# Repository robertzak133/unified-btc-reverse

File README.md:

# unified-btc-reverse

This repository contains tools, source file, hand patches, and documentation for the (nearly) complete flow for adding new features, written in C, to Browning Trail Cameras via semi-automatically generated firmware update files.  Supported cameras are BTC-7A, BTC{7,8}{E, E-HP4, E-HP5}.  That is, Browning Recon Force Advantage, and Recon Force  and Spec Ops line of cameras, models Edge, Elite HP4, and Elite HP5.

Note that installing this firmware may void the manufacturer warranty.  If you need to return a camera to the manufacture for warranty, see instructions below for "Reinstalling Factory Firmware" to first get the camera back into original factory configuration.  

## Most Recent Releases
2025-03-02: 

A major release, including new functions, and generalization of  previous functions. 

I have also updated the firmare for the HP5 cameras so that they are based on the more recent factory firmware, version "M06170F." I'm not sure what's new in this factory release, although I don't believe it addresses the "corrupt SD card" bug.  My fix for this bug remains in place.

I added support for the BTC-7A (Recon Force Advantage) model.  This firmware is based on the more recent model for the BTC-7E, and thus inherits the "capture timer" feature Bronwning introduced with the "Elite" models.

I added Several new features, described in more detail below.  These include: 

* Saving and Restoring Custom Settings

* Native Photo Quality

* External Trigger

I have also removed the "Extended SD Card" menu.  This was a lightly used, and likely obsolete function, and I needed to retire it to make room for the custom configuration code, above.

As of 2025-03-18, there is a known issue that prevents certain newer HP5 cameras from downloading this firmware (or Browning firmware, for that matter).  If the "YES" option isn't available in the "FW UPGRADE" menu, you may have one of these cameras. 

See notes below for a description of how these new features might be used.  

## Feature Description
See also articles describing features at [New Optional Features for Browning HP5 Trail Cameras](https://winterberrywildlife.ouroneacrefarm.com/2022/12/19/new-optional-features-for-browning-hp5-trail-cameras/)
and 
[Adding Features to Browning Elite HP5 Firmware](https://winterberrywildlife.ouroneacrefarm.com/2022/11/14/adding-features-to-browning-elite-hp5-firmware/)

## Released Firmware Images
If you are here for RELEASE'd firmware images themselves, you can find them below:
| Camera Model | Factory Baseline  | Current WBWL | Version  | Build Date |
|--------------|-------------------|--------------|----------|------------|
| BTC-7A | [brnbtc70.BRN](https://github.com/robertzak133/unified-btc-reverse/blob/main/targets/btc-7a/factory-firmware-images/BTC7E_2021_10_07/brnbtc70.BRN) | [brnbtc70.BRN](https://github.com/robertzak133/unified-btc-reverse/blob/main/targets/btc-7a/created-burn-images/RELEASE/brnbtc70.BRN) | WWL7A_250321R | 2025-03-21 |
| BTC-7E | [brnbtc70.BRN](https://github.com/robertzak133/unified-btc-reverse/blob/main/targets/btc-7e/factory-firmware-images/BTC7E_2021_10_07/brnbtc70.BRN) | [brnbtc70.BRN](https://github.com/robertzak133/unified-btc-reverse/blob/main/targets/btc-7e/created-burn-images/RELEASE/brnbtc70.BRN) | WWL7E_250321R | 2025-03-21 |
| BTC-8E | [brnbtc80.BRN](https://github.com/robertzak133/unified-btc-reverse/blob/main/targets/btc-8e/factory-firmware-images/BTC8E_2021_10_07/brnbtc80.BRN) | [brnbtc80.BRN](https://github.com/robertzak133/unified-btc-reverse/blob/main/targets/btc-8e/created-burn-images/RELEASE/brnbtc80.BRN) | WWL8E_250321R | 2025-03-21 |
| BTC-7E-HP4 | [brnbtc71.BRN](https://github.com/robertzak133/unified-btc-reverse/blob/main/targets/btc-7e-hp4/factory-firmware-images/2023-02-01-ns/brnbtc71.BRN) | [brnbtc71.BRN](https://github.com/robertzak133/unified-btc-reverse/blob/main/targets/btc-7e-hp4/created-burn-images/RELEASE/brnbtc71.BRN) | WWL7EH4_250321R | 2025-03-21 |
| BTC-8E-HP4 | [brnbtc81.BRN](https://github.com/robertzak133/unified-btc-reverse/blob/main/targets/btc-8e-hp4/factory-firmware-images/2023-02-01-ns/brnbtc81.BRN) | [brnbtc81.BRN](https://github.com/robertzak133/unified-btc-reverse/blob/main/targets/btc-8e-hp4/created-burn-images/RELEASE/brnbtc81.BRN) | WWL8EH4_250321R | 2025-03-21 |
| BTC-7E-HP5 | [brnbtc72.BRN](https://github.com/robertzak133/unified-btc-reverse/blob/main/targets/btc-7e-hp5/factory-firmware-images/BTC7EH5_M06170F/brnbtc72.BRN) | [brnbtc72.BRN](https://github.com/robertzak133/unified-btc-reverse/blob/main/targets/btc-7e-hp5/created-burn-images/RELEASE/brnbtc72.BRN) | WWL7EH5_250321R | 2025-03-21 |
| BTC-8E-HP5 | [brnbtc82.BRN](https://github.com/robertzak133/unified-btc-reverse/blob/main/targets/btc-8e-hp5/factory-firmware-images/BTC8EH5_M06170F/brnbtc82.BRN) | [brnbtc82.BRN](https://github.com/robertzak133/unified-btc-reverse/blob/main/targets/btc-8e-hp5/created-burn-images/RELEASE/brnbtc82.BRN) | WWL8EH5_250321R | 2025-03-21 |

## Download Instructions
- Find the copy of brnbtc7x.BRN (Recon Force) or brnbtc8x.BRN (Spec Ops) file for your camera above
- Click "Download Raw".  Resulting file should be approximateley 4-6 MBytes in length.  
- Copy this file onto an SD card at the "top level" (not into a folder on SD card).  
- Note -- the file must be named "brnbtc7x.BRN" (for Recon Force) or "brnbtc8x.BRN" (for Spec Ops), where "x" is model dependent.  Sometimes downloading from your browser will add extra characters to distinguish it from previous downloads -- e.g. "brnbtc72(1).BRN".  If this happens, rename file to eliminate the extra character. In this case, to  "brnbtc72.BRN". 

## FW install Instructions

Before installing new firmware, make sure you have batteries that will easily power the camera for the several minutes it takes for firmware upgrade. Losing power during firmware upgrade is bad, requiring that the camera be reprogrammed by the manufacturer.  

On the Camera:
- Press "Mode" button 
- Select "CAMERA SETUP"
- Select "FW UPGRADE"
- Select "YES"

Display should show "UPGRADING".  Loading the firmware should take about 20 seoconds. DO NOT TURN OFF OR REMOVE BATTERIES DURING THIS TIME! (this will "brick" the camera).  

Camera will then "Reboot" with new firmware.

Note that updating firmware resets the camera configuration settings, including the date and time. 

## Reinstalling Factory Firmware
If, for any reason, you want to get back to the factory firmware, choose the "Factory Baseline" entry in the table above to get the baseline factory image, and install that.

Note that in order to restore the factory firmware to a BTC-7A camera, it is necessary to install the factory firmware twice, in succession, in order to work around incompatiblities between the firmware loader original to the BTC-7A, and that of the BTC-7E (which I used as the baseline for the custom BTC-7A firmware).  

## Feature Summary
 * Custom Ribbon: In "Playback" menu, the date and time of the photo/video are shown is larger font at the bottom of the playback screen, making it easier to tell when the image was taken when reviewing in the field. 
 * Night Video Limit: The default manufacturer firmware limits night time (flash illuminated) videos to 20 Seconds.  This option removes that limit, allowing illuminated videos of the same duration as daylight videos.
 * Custom Info Strip: Adds "seconds" to the time of day; adds battery percent; compresses the size of the Browning logo so it doesn't extend up into the main screen space. 
 * Custom Volume/Directory/Filenames: Normally, this camera renames the SD card "volume"  to "BROWNING", in folders in DCIM called xxxBTCF, in files called IMG_xxxx.  With this modification, these labels are all taken from the camera name, as set by the user.  Note that only the first 5 and 4 characters are used for the folder and file suffix/prefix respectively.  Thus, for camera name, "MYCAMERA", the SD card will be labeled "MYCAMERA" and files can be found in DCIM/100MYCAME/MYCA0001.JPG.  Any "space" in the first 5 characters is replaced by an "underscore".
 * External Trigger: In the "DSLR" and "FLASH" settings, causes the "aim led" to turned on to trigger an external camera or external flashes.  In the "DSLR" setting, the aim test LED is set whenever a photo or video is taken.  In the "FLASH" setting the "aim led" is only turned on during low light conditions.  This can be used to trigger external flashes, which are only used at night.
 * Time and Date Format Options: Added options for time format -- 12H/24H; and date formats MM/DD/YYYY; DD/MM/YYYY; YYYY/MM/DD; and YYYYMMDD
 * IR Flash Power: Added an "Off" option to IR Flash power.  When "Off", the internal IR Flash is not used, even for night photos.  Intended for use in sets with another source of IR or White Flash illumination. 
 * Night Threshold: Lowers the amount of light required to take a color image.  Defaults to "Standard".  In the "Always Color" setting, the camera will take color photos even in darkness.  Useful with external illumination, or when converting a camera to white flash.  
 * Timelapse+ Mode Enhancements:
 
   * More Frequent Timelapse Options: I added (every) "1" and "2" second options to the Timelapse Frequency Menu.  

   * All Day/Night Timelapse Period:  The factory firmware does it's best to limit timelapse photos to daytime only.  The factory "timelapse period" menu allows you to restrict daytime photos to 1,2,3, or 4 hours after sunrise and before sunset; or to take photos "all day".  For some applications, it is desirable to take 24 hour timelapse footage.  Thus, I have added an "all day/night" menu entry.  In this mode the camera will take a photo 24/7 at the specified interval.  In the "ALL DAY/NIGHT" mode, a new .TLS file is created every at midnight, per the local clock. This creates a separate .TLS file every 24 hours.   
   * When operating in "All Day/Night" timelapse period, the CAPTURE_TIMER can be used to exclude periods of the day from timelapse photos.  
   * PIR Triggers always stored as JPG: In the factory firmware, PIR triggered photos are stored with the Timelpase photos in the .TLS file if they occur during the day.  If at night, they are stored as individual JPG images.  With my new firmware, all PIR triggered photos are stored as JPG images, making it easier to separate timelapse vs. PIR triggered images. 
   * Timelapse Format: A new menu selects whether to store images taken in Timelapse+ mode as .TLS files (factory default), or as a series of .JPG files (new feature).  This feature designed to support data processing of Timelapse images as single JPGs (e.g. an AI-based tool flow which starts with JPG images).  

* Fix to SD Corruption Issue: fixes a bug in factory firmware in which SD cards are sometimes corrupted.  This fix allows higher speed (and higer capacity) SD cards to work reliably in Edge, HP4, and HP5 models. 

 * Loading/Storing Custom Configuration to SD card: This feature allows users to save a custom configuration to a file on the SD card.  Selecting the "SAVE CUSTOM" option in the "DEFAULT SETTINGs" menu will save a copy of the current camera settings to a file on the SD card.  If an SD card contains a valid configuruation file, the "CUSTOM" entry will be selectable, and will load the configuration in the file into the camera.   SD cards can be used in multiple cameras to bring them all to a user-specific configuration quickly, and without errors associated with updating the configuration by hand. Note that configurations are camera model-specific, and separate configuration files are required for each different camera model.  The (load)"FACTORY" option returns the camera to the factory configuration.  
 * Native Photo Quality: I added a "Native" selection to the "Photo Quality" menu.  This will cause photos to be taken at the native resolution of the Sony sensor, which is 1920 * 1080 pixels [2 MPixels].  This is the same resolution used by the factory firmware to take timelapse photos, and to take "rapid burst" photos.  This feature may be useful when collecting photos for an AI-based backend processing pipeline.  

## Features no longer supported

 * Extended SD Power: Causes the CPU and SD card to remain powered on for 30 seconds after each photo or video.  This to allow shared SD card to be read by another device.  Note that during this time, the camera will not trigger.

## Build environment and Source Code

This repository contains tools and source code for building firmware images.  

This is the third reorganziation of this effort, and it is aimed at preserving as much commonality between camera platforms as possible.  For example, by containing a single set of tools and source code for all targeted cameras.

Start at [Google Colab worksheet](https://github.com/robertzak133/unified-btc-reverse/blob/main/tools/colab/2023-01-30-Unified-BTC-BRN-FIle-Creator.ipynb) 

More detailed documentation to come in future blog posts, which will be referenced here.

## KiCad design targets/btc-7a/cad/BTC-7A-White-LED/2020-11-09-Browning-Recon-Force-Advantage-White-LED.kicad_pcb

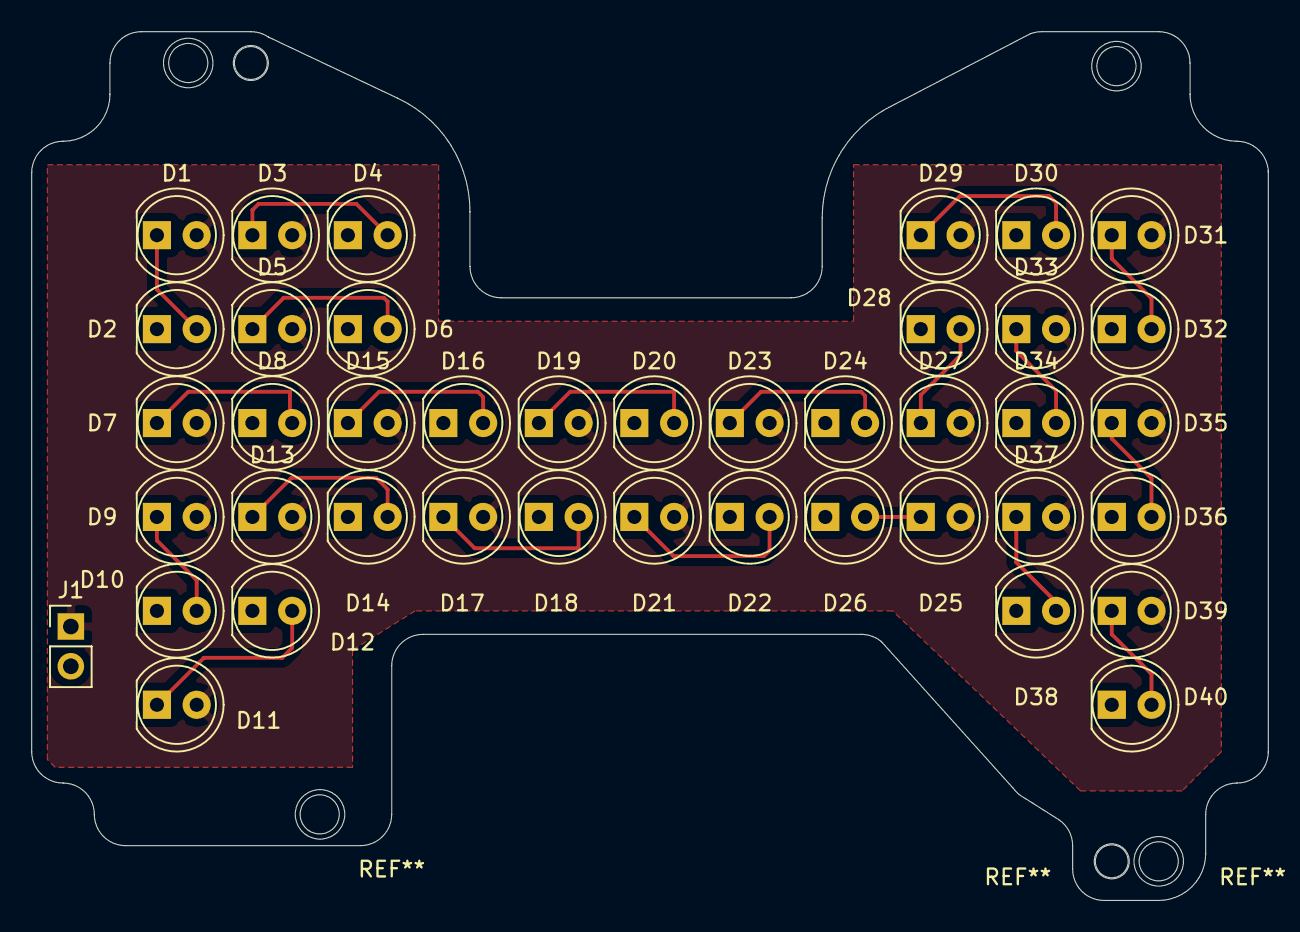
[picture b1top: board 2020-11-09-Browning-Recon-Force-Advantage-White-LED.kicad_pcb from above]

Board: 2 copper layers, 79.0 x 55.5 mm, 41 parts (0 on the bottom side), 22 nets.

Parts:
D1, D2, D3, D4, D5, D6, D7, D8, D9, D10, D11, D12, D13, D14, D15, D16, D17, D18, D19, D20, D21, D22, D23, D24, D25, D26, D27, D28, D29, D30, D31, D32, D33, D34, D35, D36, D37, D38, D39, D40: LED; LED_D5.0mm
J1: Conn_01x02; PinHeader_1x02_P2.54mm_Vertical

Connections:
LED+: D1.2, D3.2, D5.2, D7.2, D9.2, D11.2, D13.2, D15.2, D17.2, D19.2, D21.2, D23.2, D25.2, D27.2, D29.2, D31.2, D33.2, D35.2, D37.2, D39.2, J1.1
LED-: D2.1, D4.1, D6.1, D8.1, D10.1, D12.1, D14.1, D16.1, D18.1, D20.1, D22.1, D24.1, D26.1, D28.1, D30.1, D32.1, D34.1, D36.1, D38.1, D40.1, J1.2
unnamed: D1.1, D2.2
unnamed: D3.1, D4.2
unnamed: D5.1, D6.2
unnamed: D7.1, D8.2
unnamed: D9.1, D10.2
unnamed: D11.1, D12.2
unnamed: D13.1, D14.2
unnamed: D15.1, D16.2
unnamed: D17.1, D18.2
unnamed: D19.1, D20.2
unnamed: D21.1, D22.2
unnamed: D23.1, D24.2
unnamed: D25.1, D26.2
unnamed: D27.1, D28.2
unnamed: D29.1, D30.2
unnamed: D31.1, D32.2
unnamed: D33.1, D34.2
unnamed: D35.1, D36.2
unnamed: D37.1, D38.2
unnamed: D39.1, D40.2

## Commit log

2023-01-30 Updated Readme file
    Added vision, some details to README
2023-06-13 Major release
    Tools and source code for creating new firmware for 3 generations of SpecOps/Recon Force cameras -- the Edge, Elite HP4, and Elite HP5. Known bugs: threshold setting for daylight vs. night photos doe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
2023-06-15 Update README.md
    Added reference to google colab sheet; blog articles; placeholder for references to images
2023-07-04 RELEASE IMAGES
    Includes update-to-date firmware images in RELEASE directories
2023-07-04 README Update
    Added pointers to README.md
2023-07-04 Update README.md
    Note bug in some Edge cameras related to pressure and temperature readings in info strip
2023-07-07 Automatically Generate Table of Versions
    Hacked in some code to automatically create table of pointers and current version numbers. At this point, I have to hand paste this file into the readme document :(
2023-07-07 Continued Auotmatic Version update
2023-07-07 Automatic Version Table -- Bug fix
    Fixing syntax for hyperlink entries in table
2023-07-07 Automatic Version Table
    More bug fixes
2023-07-07 Bug fix to Automatic Version Table
2023-07-08 Added Aperture (Daylight Threshold)
    Found a couple of bits in the non-volatile storage extension to store the "night threshold" encoding. When set to "NO LIGHT", the camera will always take color, no flash images
2023-09-23 Foundational Bug Fixed -- Rev 2023-09-14
    Major bug fixes to updated function across all camera types. Included fixes to Bug1 and Bug2 in the database. (Pressure/temperature reading on BTC-8E -- SpecOps Edge; and Day/Night threshold). Ohers.
2023-09-23 Updated README
    Added table of current firmware images to "README". Updated documentation
2023-10-22 Fixed bugs with timelapse menu -- removed duplicated menu items and reparied "20 Second" timelapse frequency
2023-11-16 Fix to "Corrupt SD Card" Browning Bug
    Added a line of source code which insures that higher speed SD cards are operated at lower speed without waiting for errors (which can corrupt the file system)
2024-01-23 Support for EEPROM Images and Board Locations
    Added new code and tables to make it easier for folks to download EEPROM images to replace broken EEPROM Devices
2024-01-23 Fixing EEPROM.md
    Hand fixes required
2024-01-23 Update EEPROM.md
    Spell checking
2024-01-23 Fixing up EERPOM Table/Generator
    Links to EEPROM files were broken
2024-01-23 More fixes to table generator and tables
    Final fixing of URLS to EEPROM images
2024-01-23 Added Advantage EEPROM Images
    Advantage EEPROM Images to EEPROM Table
2024-02-24 Update README.md
    Added description of timelapse patches
2024-05-07 Timelapse Format Feature and bug fix for "Daylight Threshold"
    Release includes new menu item which allows user to select file format for images taken in Timelapse+ mode. .TLS for factory behavior. .JPG for new beahvior which outputs images as a series of JPG fi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
    "Daylight Threshold" update fixes bug in BTC-HP4 cameras where "low light" was actually approximately factory setting, and "standard" was much lower.
2024-05-31 New Fix for Corrupted SD Card
    There are several places in the code where it sets the internal SD clock to operate at 50 MHz (if SD card is capable). Unfortunately, hardware/firmware on the camera doesn't reliably work above 25 MH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
2024-05-31 Corrupted SD card fix -- Part 2
    Oops -- missed some file in earlier release
2024-06-07 "All Day/Night" Timelapse Period
    All Day/Night Timelapse Period: The factory firmware does it's best to limit timelapse photos to daytime only. The factory "timelapse period" menu allows you to restrict daytime photos to 1,2,3, or 4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
2024-09-10 Update README.md
    Sentence on voiding manufacturer warranty
2025-03-22 Major Release 20250321R
    A major release, including new functions, and generalization of previous functions.
    I have also updated the firmare for the HP5 cameras so that they are based on the more recent factory firmware, version "M06170F." I'm not sure what's new in this factory release, although I don't be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
    I added support for the BTC-7A (Recon Force Advantage) model. This firmware is based on the more recent model for the BTC-7E, and thus inherits the "capture timer" feature Bronwning introduced with t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
    I added Several new features, described in more detail below. These include:
    * Savi
2025-05-01 BTC-7A "upside down image" bug fix
    Model-specific change to hand patch list to fix a bug with BTC-7A support in which image from sensor was upside down on preview screen, in photos, and on video.
2025-05-01 BTC-7A fix (part 2)
    Remainder of files
